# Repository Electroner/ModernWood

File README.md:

# ModernWood keyboard  

En este repositorio encontrarás desde los datasheet de cada parte que he usado hasta los archivos originales del AutoCAD, con todos los archivos descargados deberías ser capaz de poder crear y manufacturar este teclado sin ningún problema.

Este teclado usa un ESP32-S3 como controlador y un decodificador/Demultiplexor 74HC154D 4-a-16, Suficiente para conseguir un tiempo de polling igual o superior a los mejores teclados comerciales actuales (20kHz). Pruebas realizadas con el código actual. Además se ha decidido "prescindir" de un teclado numérico real, y lo que se ha hecho es conectar los números del numpad a los números de la parte superior del teclado, por lo que las teclas tanto del numpad como los de la parte superior son los mismos, al igual con el intro y "." (Ver Esquemática).

Para el cuerpo del teclado se ha optado por omitir de forma completa el Plate o panel superior, ya que dificulta el mantenimiento y el montaje. Se ha optado solo por poner una ventana de metacrilato en la parte de la electrónica para cubrirla de forma semicompleja y protegerla de golpes. La base del teclado es de madera. Esta será la que más guste al usuario, aunque se recomiendan jatoba, sucupira o mansonia.

Este además dispone de una pantalla donde se encontraran todas las configuraciones del teclado, además de la opción para habilitar o deshabilitar el funcionamiento por bluetooth.

## Imagenes

---------------------------------------------------------------------------------------------

---------------------------------------------------------------------------------------------

Vista Previa de la PCB:

Schematic:

### Piezas (Electronica)

```plaintext
PARTS

MUX 		| CD74HC154M96 (SOIC-24-300mil) | x1
CAPACITOR 	| 293D105X9035A2TE3 1uF (1206) 	| x5
RESISTOR	| RT0805BRD071KL 1k (0805)	| x5
RESISTOR	| RC0805FR-071ML 1M (0805)	| x3
RESISTOR	| 0805W8F2004T5E 2M (0805)	| x2
RESISTOR	| RC0805FR-073M74L 4M (0805)	| x1 (Is better if its 3.7M)
BATT PROTECTOR	| TP4056 (C725790) 		| x1
BATT PROTECTOR	| DW01A (SOT23-6) 		| x1
BATT PROTECTOR	| ME6211C33M5G (SOT-23-5) 	| x1
BATT PROTECTOR	| FS8205A (TSSOP-8) 		| x1
MAIN CHIP	| ESP32-S3 (SMD,18x25.5mm)	| x1
LEDS		| WS2812B (C114586)		| x10
DIODE		| 1N5819W (SOD123FL)		| x96
```

## Recursos Usados

-   [Alguna Investigacion y aprendizaje](https://github.com/w4ilun/pocket-keyboard)

Y varias paginas para datos concretos como funciones en eagle,ayuda con el bootloader y ejemplos de otros teclados.

-   [Ayuda con el bootloader](https://forum.arduino.cc/t/burning-bootloader-to-custom-board-atmega32u4/890015)
-   [Ayuda con el N-key](https://forum.arduino.cc/t/how-to-program-n-key-rollover-atmega32u4/938418)

## Software Usado

-   [Editor de Layaout Teclado](http://www.keyboard-layout-editor.com/)
-   [Autocad](https://www.autodesk.es/products/autocad/overview?term=1-YEAR&tab=subscription)
-   [FreeCad](https://www.freecadweb.org/)
-   [Eagle](https://www.autodesk.com/products/eagle/free-download)
-   [Componentes Eagle](https://componentsearchengine.com/)
-   [Produccion de la PCB](https://jlcpcb.com/)
-   [Compra de los componentes](https://lcsc.com/)
-   [Corte de metacrilato (Tienda Local)](https://ecoplasticlaser.com/)

## Actualizar las librerias

> [!IMPORTANT]  
> Si las librerias se actualizan en PlatformIO:
```
Cambiar 
#include <User_Setup.h> // en User_Setup_Select.h a:

//#include <User_Setup.h>
#include <../TFT_eSPI_Setups/Setup_ST7735_ESP80x160.h>
```

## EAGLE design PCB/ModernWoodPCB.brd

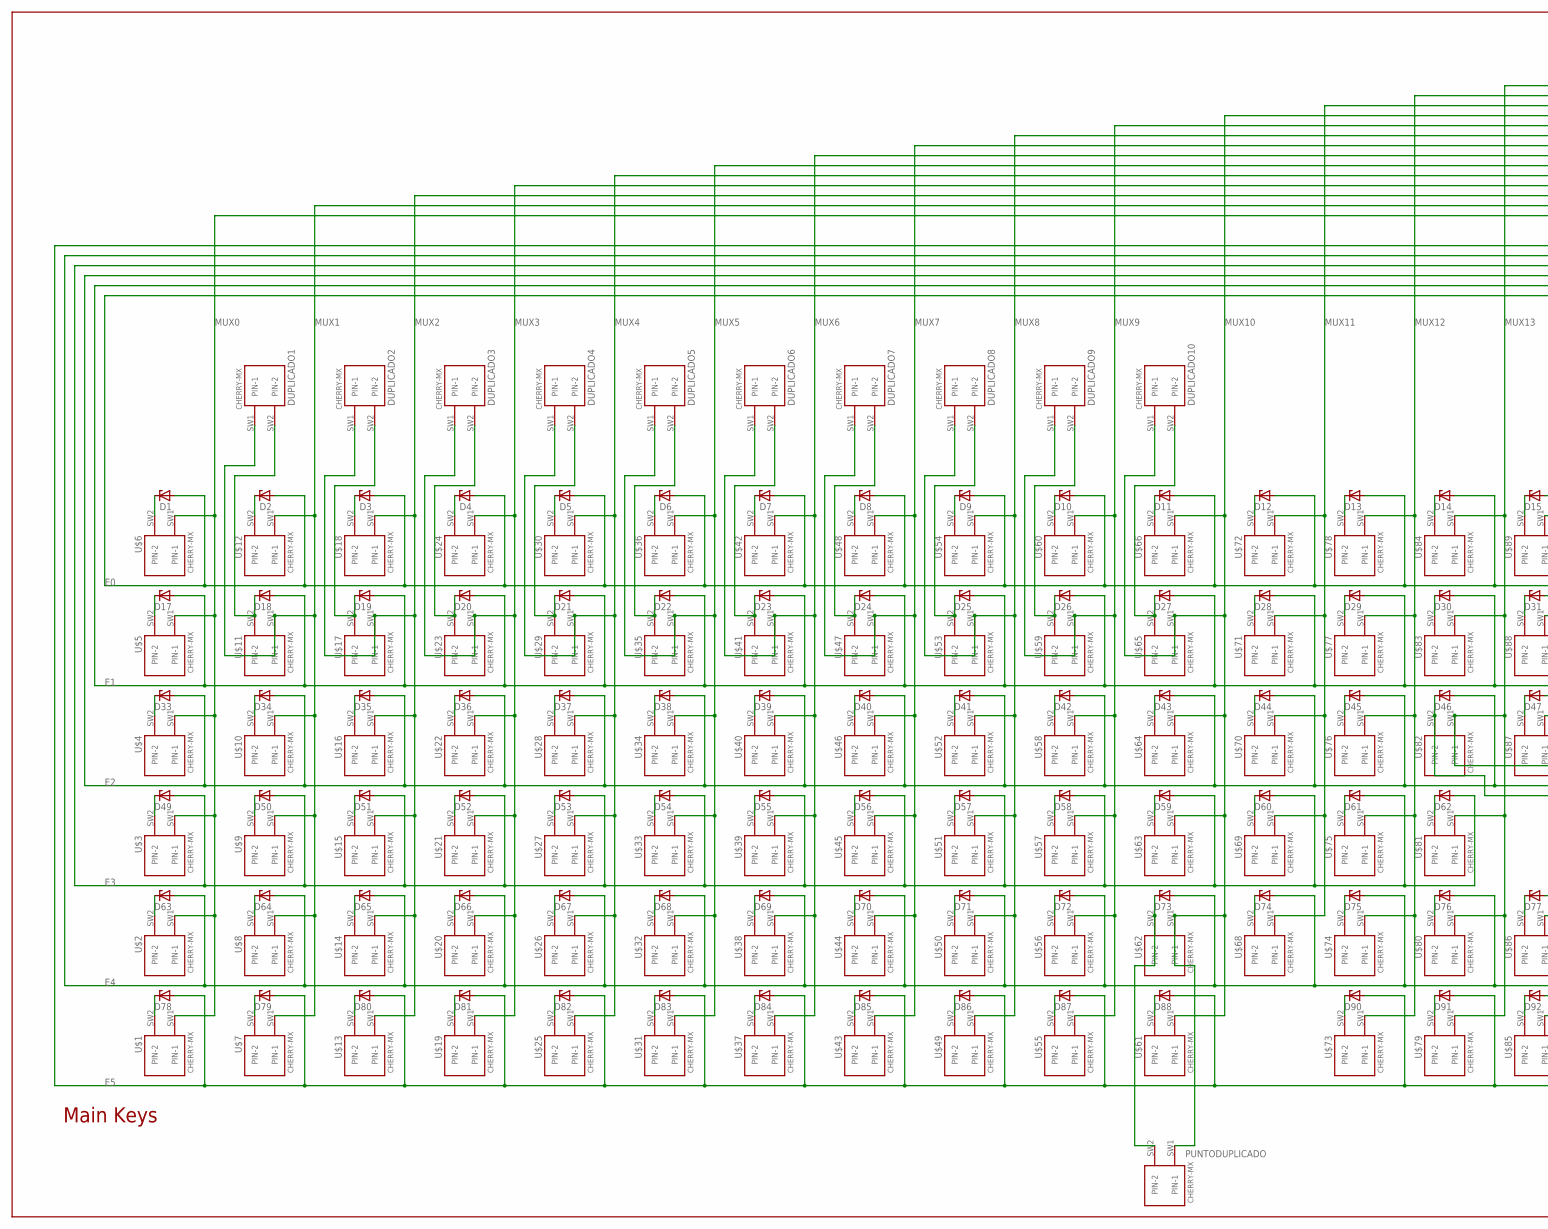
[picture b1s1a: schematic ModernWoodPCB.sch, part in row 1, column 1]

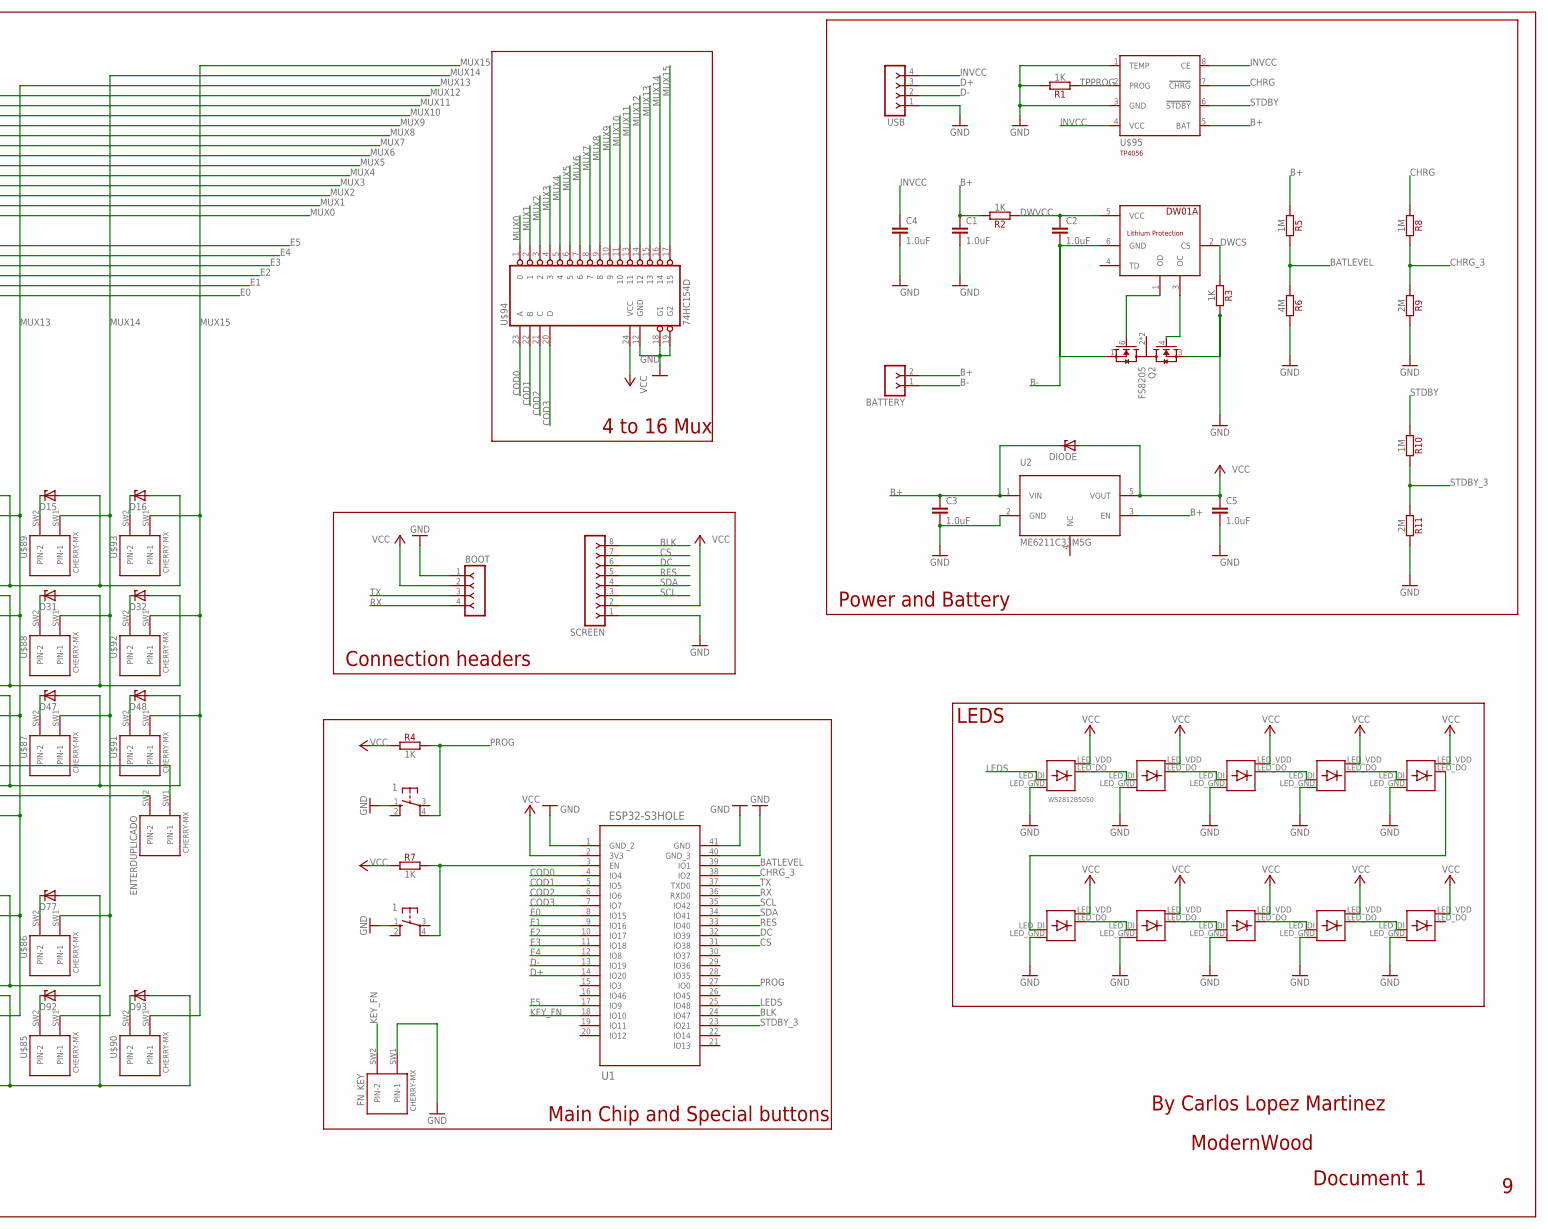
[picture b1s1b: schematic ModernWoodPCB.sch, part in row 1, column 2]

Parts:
BATTERY: F-1X02-SIP-100-40; SIP-100-02-40
BOOT: BOOT; SIP-100-04-32
BUTTON, BUTTON1: 1; B3F-10XX
C1, C2, C3, C4, C5: 1.0uF; 1206
D1, D2, D3, D4, D5, D6, D7, D8, D9, D10, D11, D12, D13, D14, D15, D16, D17, D18, D19, D20, D21, D22, D23, D24, D25, D26, D27, D28, D29, D30, D31, D32, D33, D34, D35, D36, D37, D38, D39, D40, D41, D42, D43, D44, D45, D46, D47, D48, D49, D50, D51, D52, D53, D54, D55, D56, D57, D58, D59, D60, D61, D62, D63, D64, D65, D66, D67, D68, D69, D70, D71, D72, D73, D74, D75, D76, D77, D78, D79, D80, D81, D82, D83, D84, D85, D86, D87, D88, D90, D91, D92, D93: ZENER-DIODE-SOD123; SOD123FL
DIODE: ZENER-DIODE-SOD123; SOD123FL
DUPLICADO1, DUPLICADO2, DUPLICADO3, DUPLICADO4, DUPLICADO5, DUPLICADO6, DUPLICADO7, DUPLICADO8, DUPLICADO9, DUPLICADO10: CHERRY-MX
ENTERDUPLICADO: CHERRY-MX
FN_KEY: CHERRY-MX
PUNTODUPLICADO: CHERRY-MX
Q2: FS8205; SOT95P280X145-6N
R1, R2, R3, R4, R7: 1K; R-0805
R5, R8, R10: 1M; R-0805
R6: 4M; R-0805
R9, R11: 2M; R-0805
SCREEN: F-1X08-SIP-100-40; SIP-100-08-40
U1: ESP32-S3HOLE
U2: ME6211C33M5G
U$1, U$2, U$3, U$4, U$5, U$6, U$7, U$8, U$9, U$10, U$11, U$12, U$13, U$14, U$15, U$16, U$17, U$18, U$19, U$20, U$21, U$22, U$23, U$24, U$25, U$26, U$27, U$28, U$29, U$30, U$31, U$32, U$33, U$34, U$35, U$36, U$37, U$38, U$39, U$40, U$41, U$42, U$43, U$44, U$45, U$46, U$47, U$48, U$49, U$50, U$51, U$52, U$53, U$54, U$55, U$56, U$57, U$58, U$59, U$60, U$61, U$62, U$63, U$64, U$65, U$66, U$68, U$69, U$70, U$71, U$72, U$73, U$74, U$75, U$76, U$77, U$78, U$79, U$80, U$81, U$82, U$83, U$84, U$85, U$86, U$87, U$88, U$89, U$90, U$91, U$92, U$93: CHERRY-MX
U$67, U$97, U$98, U$99, U$100, U$101, U$102, U$103, U$104, U$105: WS2812B5050
U$94: 74HC154D
U$95: TP4056; SOT23-8
U$96: DW01A; SOT23-6
USB: F-1X04-SIP-100-32; SIP-100-04-32

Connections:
B+: BATTERY.2, C1.1, C3.1, DIODE.C, R2.2, R5.1, U2.1 (VIN), U2.3 (EN), U$95.5 (BAT)
B-: BATTERY.1, C2.2, Q2.1 (S1), U$96.6 (GND)
BATLEVEL: R5.2, R6.1, U1.39 (IO1)
BLK: SCREEN.8, U1.24 (IO47)
CHRG: R8.1, U$95.7 (!CHRG)
CHRG_3: R8.2, R9.1, U1.38 (IO2)
COD0: U1.4 (IO4), U$94.23 (A)
COD1: U1.5 (IO5), U$94.22 (B)
COD2: U1.6 (IO6), U$94.21 (C)
COD3: U1.7 (IO7), U$94.20 (D)
CS: SCREEN.7, U1.31 (IO38)
D+: U1.14 (IO20), USB.3
D-: U1.13 (IO19), USB.2
DC: SCREEN.6, U1.32 (IO39)
DWCS: R3.1, U$96.2 (CS)
DWVCC: C2.1, R2.1, U$96.5 (VCC)
E0: D1.A, D2.A, D3.A, D4.A, D5.A, D6.A, D7.A, D8.A, D9.A, D10.A, D11.A, D12.A, D13.A, D14.A, D15.A, D16.A, U1.8 (IO15)
E1: D17.A, D18.A, D19.A, D20.A, D21.A, D22.A, D23.A, D24.A, D25.A, D26.A, D27.A, D28.A, D29.A, D30.A, D31.A, D32.A, U1.9 (IO16)
E2: D33.A, D34.A, D35.A, D36.A, D37.A, D38.A, D39.A, D40.A, D41.A, D42.A, D43.A, D44.A, D45.A, D46.A, D47.A, D48.A, U1.10 (IO17)
E3: D49.A, D50.A, D51.A, D52.A, D53.A, D54.A, D55.A, D56.A, D57.A, D58.A, D59.A, D60.A, D61.A, D62.A, U1.11 (IO18)
E4: D63.A, D64.A, D65.A, D66.A, D67.A, D68.A, D69.A, D70.A, D71.A, D72.A, D73.A, D74.A, D75.A, D76.A, D77.A, U1.12 (IO8)
E5: D78.A, D79.A, D80.A, D81.A, D82.A, D83.A, D84.A, D85.A, D86.A, D87.A, D88.A, D90.A, D91.A, D92.A, D93.A, U1.17 (IO9)
EN: BUTTON1.4 (P1), R7.2, U1.3 (EN)
GND: BOOT.1, BUTTON.1 (S), BUTTON1.1 (S), C1.2, C3.2, C4.2, C5.2, FN_KEY.SW1 (PIN-1), Q2.3 (S2), R1.2, R3.2, R6.2, R9.2, R11.2, SCREEN.1, U1.1 (GND_2), U1.40 (GND_3), U1.41 (GND), U2.2 (GND), U$67.LED_GND, U$94.12 (GND), U$94.18 (G1), U$94.19 (G2), U$95.1 (TEMP), U$95.3 (GND), U$97.LED_GND, U$98.LED_GND, U$99.LED_GND, U$100.LED_GND, U$101.LED_GND, U$102.LED_GND, U$103.LED_GND, U$104.LED_GND, U$105.LED_GND, USB.1
INVCC: C4.1, U$95.4 (VCC), U$95.8 (CE), USB.4
KEY_FN: FN_KEY.SW2 (PIN-2), U1.18 (IO10)
LEDS: U1.25 (IO48), U$67.LED_DI
MUX0: U$1.SW1 (PIN-1), U$2.SW1 (PIN-1), U$3.SW1 (PIN-1), U$4.SW1 (PIN-1), U$5.SW1 (PIN-1), U$6.SW1 (PIN-1), U$94.1 (0)
MUX1: DUPLICADO1.SW1 (PIN-1), U$7.SW1 (PIN-1), U$8.SW1 (PIN-1), U$9.SW1 (PIN-1), U$10.SW1 (PIN-1), U$11.SW1 (PIN-1), U$12.SW1 (PIN-1), U$94.2 (1)
MUX2: DUPLICADO2.SW1 (PIN-1), U$13.SW1 (PIN-1), U$14.SW1 (PIN-1), U$15.SW1 (PIN-1), U$16.SW1 (PIN-1), U$17.SW1 (PIN-1), U$18.SW1 (PIN-1), U$94.3 (2)
MUX3: DUPLICADO3.SW1 (PIN-1), U$19.SW1 (PIN-1), U$20.SW1 (PIN-1), U$21.SW1 (PIN-1), U$22.SW1 (PIN-1), U$23.SW1 (PIN-1), U$24.SW1 (PIN-1), U$94.4 (3)
MUX4: DUPLICADO4.SW1 (PIN-1), U$25.SW1 (PIN-1), U$26.SW1 (PIN-1), U$27.SW1 (PIN-1), U$28.SW1 (PIN-1), U$29.SW1 (PIN-1), U$30.SW1 (PIN-1), U$94.5 (4)
MUX5: DUPLICADO5.SW1 (PIN-1), U$31.SW1 (PIN-1), U$32.SW1 (PIN-1), U$33.SW1 (PIN-1), U$34.SW1 (PIN-1), U$35.SW1 (PIN-1), U$36.SW1 (PIN-1), U$94.6 (5)
MUX6: DUPLICADO6.SW1 (PIN-1), U$37.SW1 (PIN-1), U$38.SW1 (PIN-1), U$39.SW1 (PIN-1), U$40.SW1 (PIN-1), U$41.SW1 (PIN-1), U$42.SW1 (PIN-1), U$94.7 (6)
MUX7: DUPLICADO7.SW1 (PIN-1), U$43.SW1 (PIN-1), U$44.SW1 (PIN-1), U$45.SW1 (PIN-1), U$46.SW1 (PIN-1), U$47.SW1 (PIN-1), U$48.SW1 (PIN-1), U$94.8 (7)
MUX8: DUPLICADO8.SW1 (PIN-1), U$49.SW1 (PIN-1), U$50.SW1 (PIN-1), U$51.SW1 (PIN-1), U$52.SW1 (PIN-1), U$53.SW1 (PIN-1), U$54.SW1 (PIN-1), U$94.9 (8)
MUX9: DUPLICADO9.SW1 (PIN-1), U$55.SW1 (PIN-1), U$56.SW1 (PIN-1), U$57.SW1 (PIN-1), U$58.SW1 (PIN-1), U$59.SW1 (PIN-1), U$60.SW1 (PIN-1), U$94.10 (9)
MUX10: DUPLICADO10.SW1 (PIN-1), PUNTODUPLICADO.SW1 (PIN-1), U$61.SW1 (PIN-1), U$62.SW1 (PIN-1), U$63.SW1 (PIN-1), U$64.SW1 (PIN-1), U$65.SW1 (PIN-1), U$66.SW1 (PIN-1), U$94.11 (10)
MUX11: U$68.SW1 (PIN-1), U$69.SW1 (PIN-1), U$70.SW1 (PIN-1), U$71.SW1 (PIN-1), U$72.SW1 (PIN-1), U$94.13 (11)
MUX12: U$73.SW1 (PIN-1), U$74.SW1 (PIN-1), U$75.SW1 (PIN-1), U$76.SW1 (PIN-1), U$77.SW1 (PIN-1), U$78.SW1 (PIN-1), U$94.14 (12)
MUX13: ENTERDUPLICADO.SW1 (PIN-1), U$79.SW1 (PIN-1), U$80.SW1 (PIN-1), U$81.SW1 (PIN-1), U$82.SW1 (PIN-1), U$83.SW1 (PIN-1), U$84.SW1 (PIN-1), U$94.15 (13)
MUX14: U$85.SW1 (PIN-1), U$86.SW1 (PIN-1), U$87.SW1 (PIN-1), U$88.SW1 (PIN-1), U$89.SW1 (PIN-1), U$94.16 (14)
MUX15: U$90.SW1 (PIN-1), U$91.SW1 (PIN-1), U$92.SW1 (PIN-1), U$93.SW1 (PIN-1), U$94.17 (15)
unnamed: D33.C, U$4.SW2 (PIN-2)
unnamed: D34.C, U$10.SW2 (PIN-2)
unnamed: D35.C, U$16.SW2 (PIN-2)
unnamed: D36.C, U$22.SW2 (PIN-2)
unnamed: D17.C, U$5.SW2 (PIN-2)
unnamed: D1.C, U$6.SW2 (PIN-2)
unnamed: D37.C, U$28.SW2 (PIN-2)
unnamed: D38.C, U$34.SW2 (PIN-2)
unnamed: D39.C, U$40.SW2 (PIN-2)
unnamed: D40.C, U$46.SW2 (PIN-2)
unnamed: D18.C, DUPLICADO1.SW2 (PIN-2), U$11.SW2 (PIN-2)
unnamed: D2.C, U$12.SW2 (PIN-2)
unnamed: D41.C, U$52.SW2 (PIN-2)
unnamed: D42.C, U$58.SW2 (PIN-2)
unnamed: D43.C, U$64.SW2 (PIN-2)
unnamed: D44.C, U$70.SW2 (PIN-2)
unnamed: D19.C, DUPLICADO2.SW2 (PIN-2), U$17.SW2 (PIN-2)
unnamed: D3.C, U$18.SW2 (PIN-2)
unnamed: D45.C, U$76.SW2 (PIN-2)
unnamed: D47.C, U$87.SW2 (PIN-2)
unnamed: D48.C, U$91.SW2 (PIN-2)
unnamed: D62.C, U$81.SW2 (PIN-2)
unnamed: D20.C, DUPLICADO3.SW2 (PIN-2), U$23.SW2 (PIN-2)
unnamed: D4.C, U$24.SW2 (PIN-2)
unnamed: D61.C, U$75.SW2 (PIN-2)
unnamed: D60.C, U$69.SW2 (PIN-2)
unnamed: D59.C, U$63.SW2 (PIN-2)
unnamed: D58.C, U$57.SW2 (PIN-2)
unnamed: D21.C, DUPLICADO4.SW2 (PIN-2), U$29.SW2 (PIN-2)
unnamed: D5.C, U$30.SW2 (PIN-2)
unnamed: Q2.6 (G1), U$96.1 (OD)
unnamed: Q2.4 (G2), U$96.3 (OC)
unnamed: U$97.LED_DO, U$98.LED_DI
unnamed: D57.C, U$51.SW2 (PIN-2)
unnamed: D56.C, U$45.SW2 (PIN-2)
unnamed: D55.C, U$39.SW2 (PIN-2)
unnamed: D54.C, U$33.SW2 (PIN-2)
unnamed: D22.C, DUPLICADO5.SW2 (PIN-2), U$35.SW2 (PIN-2)
unnamed: D6.C, U$36.SW2 (PIN-2)
unnamed: D53.C, U$27.SW2 (PIN-2)
unnamed: D52.C, U$21.SW2 (PIN-2)
unnamed: D51.C, U$15.SW2 (PIN-2)
unnamed: D50.C, U$9.SW2 (PIN-2)
unnamed: D23.C, DUPLICADO6.SW2 (PIN-2), U$41.SW2 (PIN-2)
unnamed: D7.C, U$42.SW2 (PIN-2)
unnamed: D49.C, U$3.SW2 (PIN-2)
unnamed: D63.C, U$2.SW2 (PIN-2)
unnamed: D64.C, U$8.SW2 (PIN-2)
unnamed: D65.C, U$14.SW2 (PIN-2)
unnamed: D24.C, DUPLICADO7.SW2 (PIN-2), U$47.SW2 (PIN-2)
unnamed: D8.C, U$48.SW2 (PIN-2)
unnamed: D66.C, U$20.SW2 (PIN-2)
unnamed: D67.C, U$26.SW2 (PIN-2)
unnamed: D68.C, U$32.SW2 (PIN-2)
unnamed: D69.C, U$38.SW2 (PIN-2)
unnamed: D25.C, DUPLICADO8.SW2 (PIN-2), U$53.SW2 (PIN-2)
unnamed: D9.C, U$54.SW2 (PIN-2)
unnamed: D70.C, U$44.SW2 (PIN-2)
unnamed: D71.C, U$50.SW2 (PIN-2)
unnamed: D72.C, U$56.SW2 (PIN-2)
unnamed: D74.C, U$68.SW2 (PIN-2)
unnamed: D26.C, DUPLICADO9.SW2 (PIN-2), U$59.SW2 (PIN-2)
unnamed: D10.C, U$60.SW2 (PIN-2)
unnamed: D75.C, U$74.SW2 (PIN-2)
unnamed: D73.C, PUNTODUPLICADO.SW2 (PIN-2), U$62.SW2 (PIN-2)
unnamed: D76.C, U$80.SW2 (PIN-2)
unnamed: D77.C, U$86.SW2 (PIN-2)
unnamed: D27.C, DUPLICADO10.SW2 (PIN-2), U$65.SW2 (PIN-2)
unnamed: D11.C, U$66.SW2 (PIN-2)
unnamed: D93.C, U$90.SW2 (PIN-2)
unnamed: D92.C, U$85.SW2 (PIN-2)
unnamed: D91.C, U$79.SW2 (PIN-2)
unnamed: D90.C, U$73.SW2 (PIN-2)
unnamed: D28.C, U$71.SW2 (PIN-2)
unnamed: D12.C, U$72.SW2 (PIN-2)
unnamed: U$98.LED_DO, U$99.LED_DI
unnamed: D88.C, U$61.SW2 (PIN-2)
unnamed: D87.C, U$55.SW2 (PIN-2)
unnamed: D86.C, U$49.SW2 (PIN-2)
unnamed: D29.C, U$77.SW2 (PIN-2)
unnamed: D13.C, U$78.SW2 (PIN-2)
unnamed: D85.C, U$43.SW2 (PIN-2)
unnamed: D84.C, U$37.SW2 (PIN-2)
unnamed: D83.C, U$31.SW2 (PIN-2)
unnamed: D46.C, ENTERDUPLICADO.SW2 (PIN-2), U$82.SW2 (PIN-2)
unnamed: D30.C, U$83.SW2 (PIN-2)
unnamed: D14.C, U$84.SW2 (PIN-2)
unnamed: D82.C, U$25.SW2 (PIN-2)
unnamed: D81.C, U$19.SW2 (PIN-2)
unnamed: D80.C, U$13.SW2 (PIN-2)
unnamed: D31.C, U$88.SW2 (PIN-2)
unnamed: D15.C, U$89.SW2 (PIN-2)
unnamed: D79.C, U$7.SW2 (PIN-2)
unnamed: D78.C, U$1.SW2 (PIN-2)
unnamed: D32.C, U$92.SW2 (PIN-2)
unnamed: D16.C, U$93.SW2 (PIN-2)
unnamed: U$99.LED_DO, U$100.LED_DI
unnamed: U$100.LED_DO, U$101.LED_DI
unnamed: U$101.LED_DO, U$102.LED_DI
unnamed: U$102.LED_DO, U$103.LED_DI
unnamed: U$103.LED_DO, U$104.LED_DI
unnamed: U$104.LED_DO, U$105.LED_DI
unnamed: U$67.LED_DO, U$97.LED_DI
PROG: BUTTON.4 (P1), R4.2, U1.27 (IO0)
RES: SCREEN.5, U1.33 (IO40)
RX: BOOT.4, U1.36 (RXD0)
SCL: SCREEN.3, U1.35 (IO42)
SDA: SCREEN.4, U1.34 (IO41)
STDBY: R10.1, U$95.6 (!STDBY)
STDBY_3: R10.2, R11.1, U1.23 (IO21)
TPPROG: R1.1, U$95.2 (PROG)
TX: BOOT.3, U1.37 (TXD0)
VCC: BOOT.2, C5.1, DIODE.A, R4.1, R7.1, SCREEN.2, U1.2 (3V3), U2.5 (VOUT), U$67.LED_VDD, U$94.24 (VCC), U$97.LED_VDD, U$98.LED_VDD, U$99.LED_VDD, U$100.LED_VDD, U$101.LED_VDD, U$102.LED_VDD, U$103.LED_VDD, U$104.LED_VDD, U$105.LED_VDD

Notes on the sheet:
ModernWood
Document 1
By Carlos Lopez Martinez
LEDS
Main Chip and Special buttons
Connection headers
Power and Battery
4 to 16 Mux
Main Keys

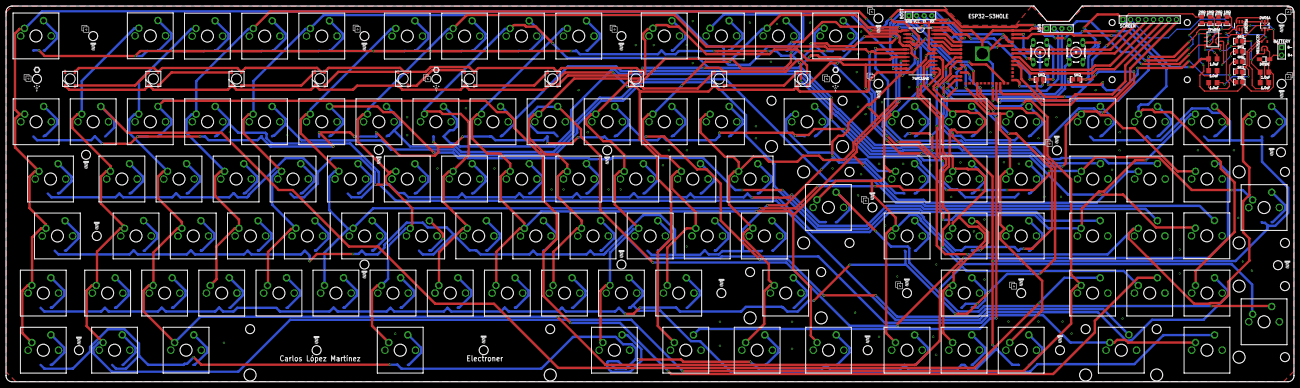
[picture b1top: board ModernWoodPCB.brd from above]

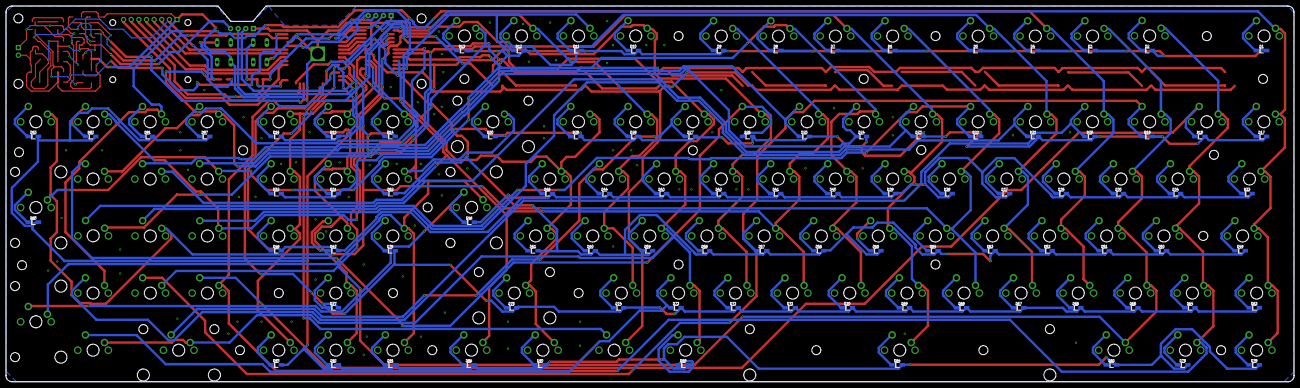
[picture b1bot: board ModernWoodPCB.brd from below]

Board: 2 copper layers, 428.5 x 125.0 mm, 236 parts (92 on the bottom side), 156 nets.

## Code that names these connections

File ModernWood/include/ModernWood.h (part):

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
extern bool configurationReseted;

#define COD0 4  //Output pin X0 (GPIO4)
#define COD1 5  //Output pin X1 (GPIO5)
#define COD2 6  //Output pin X2 (GPIO6)
#define COD3 7  //Output pin X3 (GPIO7)

#define E0 15   //Input pin E0 
#define E1 16   //Input pin E1 
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extern int* SubMenuConfigVar[SizeSubMenuConfig];

enum SubMenuBrightness {_BrightnessLeds, _BrightnessDisplay, SizeSubMenuBrightness}; 
const String SubMenuBrightnessText[SizeSubMenuBrightness] = {"Brightness Leds", "Brightness Display"};
const String SubMenuBrightnessKeys[SizeSubMenuBrightness] = {"BRILED", "BRIDIS"};
const String SubMenuBrightnessVarType[SizeSubMenuBrightness] = {"int", "int"};
extern int* SubMenuBrightnessVar[SizeSubMenuBrightness];

enum SubMenuLeds {_EnableLeds, _LedsColor, _LedsMode, _LedsSpeed, SizeSubMenuLeds};
const String SubMenuLedsText[SizeSubMenuLeds] = {"Enable Leds", "Leds Color", "Leds Mode", "Leds Speed"};
const String SubMenuLedsKeys[SizeSubMenuLeds] = {"ENALED", "LEDCOL", "LEDMOD", "LEDSPE"};
const String SubMenuLedsVarType[SizeSubMenuLeds] = {"bool", "rgb", "int", "int"};
extern int* SubMenuLedsVar[SizeSubMenuLeds];
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
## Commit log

2023-01-24 Started Proyect
2023-06-27 First
2023-06-27 RGB AND PROGRAM READY
2023-06-27 Deleted Extra Files
2023-06-28 All interruptions done
2023-07-01 Screen Working
2023-07-01 Adding the modified files of the screen TFT
2023-07-01 ModernWood Icon added
2023-07-03 Animations and Screen battery and connections tested
2023-07-03 Added the Icons and the screen is now working
2023-07-04 Fixed Interruptions and FN mode for Keyboard
2023-07-05 Added ModerWood Functions
2023-07-08 Release all in Display Mode
2023-07-09 Pins fixed 8 and 2
2023-08-01 Added The inverted images and selecctor for the menu
2023-08-03 Arrow keys navigate, Enter selects, Working.
2023-08-03 Renamed all comments and variables to English
2023-08-04 Enter Key working and done
2023-08-04 Added badge to README.md
2023-08-04 Fixed Function for printing, added enter and ESC working
2023-08-04 Removed a file
2023-08-15 Added The menu suboptions and make it scalable, Minor Fixes
2023-08-16 Changed value of configuration parameters submenu
2023-08-16 Moved all variables to the header file. Added a new variable for the Menu array
2023-09-11 Added the schematic of the pcb autocad
2023-09-13 Created RGB Custom class and created all the variables of the menu
2023-09-14 Fixed minor bugs and added Varible Show correctly in menu
2023-09-15 Added the selector to the subMenu.
2023-09-15 Temporal commit
2023-09-15 Refactor the code and Make the heads of the config funcions
2023-09-15 Menu and control of parameters working just rest saving it to EEPROM
2023-09-29 Turned built in led on for debug
2023-10-09 New directory and changed the tiny dxf sketch
2023-10-10 Added the modules folder and configured the project added also a Version example
2023-10-10 Added the Function pointers array and set the default None Function in Base.h
2023-10-11 Added the especal mode function and set all the flags right for using the FN
2023-10-12 Added a Function to exit Modules easily.
2023-10-18 Fixed Inline error with exitModule() Function and added temperature Monitoring.
2023-10-18 Changed The autocad Sketch
2023-10-18 Added the 3º view on the Sketch
2023-10-24 Changed PCB and added the TP4056 Parts, also changed diode types.
2023-10-28 Created the Led hole for keys library.
2023-11-04 Make the connections for the Battery and Power circuits
2023-11-23 Make the screen DXF and added it to .pcb board
2023-11-23 Changed Capacitor and resistor type
2023-11-24 Added the esp32 chip connections lines in .sch
2023-11-25 Finished the power circuit for the keyboard
2023-11-25 Finished .sch
2023-11-26 Added new holes and changed the pcb layaout to fit the usb connector
2023-11-27 Finished PCB Board and Schematic
2023-11-28 Fixed PCB holes and dimensions, improved GND Plane. Ready for Production
2023-11-28 Created the Parts file and the step file
2023-11-28 Fix value in parts
2023-11-28 Fixed TX/RX Lenght
2023-11-30 Fixed Leds datasheet
2024-02-20 Revision 2 of PCB and Finished
2024-02-20 Added Mark for JLCPB
2024-02-21 Fixed 5V on Tp4056 status pins
2024-02-21 Added Text to PCB
2024-02-22 Fixed value texts for smd resistors
2024-02-22 Updated Parts.txt for new resistors
2024-02-22 Updated all doccuments related to PCB
2024-02-22 Updated version
2024-02-22 Changed Images
2024-02-22 Removed a error in PCB Silkscreen layer
2024-02-22 Removed files
2024-03-01 Updated ModernWood TFT_eSPI library
2024-03-01 Updated and added Bluetooth functions and everythings works
2024-03-01 Everything up to date
2024-04-04 New review of Schematic and added a voltage regulator diode protection
2024-04-17 Added an option to control debug from a host keyboard
2024-04-17 Added Rainbow Mode for leds. Also make ble enable dissable.
2024-04-17 Fixed on/off bluetooth keyboard
2024-05-15 Preferences and EEPROM configuration working
2024-05-16 Fixed led color and EEPROM loading color, also adjusted the voltaje of battery mapping
2024-05-20 All keyboard working
2024-05-20 Updated Planos
2024-05-22 Added HSV Color and better led performance.
2024-05-23 everything working. only energy save mode left.
2024-05-23 Created energyBracnh
2024-05-23 Done creating the power save mode
2024-05-27 Added Sleep mode
2024-05-28 Eveything working
2024-05-28 Added define for sleep time and fixed ble battery update
2024-05-28 Added the firmware.bin to upload without the src
2024-06-01 First phyisical test passing
2024-06-01 Fixed leds and minors logics
2024-06-10 Fixed ble initialization and on/off
2024-06-22 Added the product images
2024-06-22 Finished
2024-06-22 Changed image 01
2024-07-01 Minor Fixes for starting up the board with low amperage
2024-07-01 Updated the binaries
2024-09-16 Fixed minor screen bugs when editing config

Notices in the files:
parts and their libraries:
con-headers-jp: Copyright (C) 2008, Bob Starr
SparkFun-Capacitors: Licensing: Creative Commons ShareAlike 4.0 International - https://creativecommons.org/licenses/by-sa/4.0
COPYRIGHT: Copyright (C) 2023 Ultra Librarian. All rights reserved.
